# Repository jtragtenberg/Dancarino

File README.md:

# Jerimum
open source IMU

23/10/2015
Fala Rodrigo, novas instruções para o commit "adicionei arquivos de arduino e processing do Motioner para ler RAW e…":

Pelo código estar uma gambiarra só, primeiro estude os quaternions e só depois mande esse código novo pro arduino pra ver os dados RAW... 
e pra te ajudar no descoberta de como os quaternions funcionam:
q = <qw,qx,qy,qz> = <cos(teta/2) , x*sen(teta/2) , y*sen(teta/2) , z*sen(teta/2)>
onde x,y,z é o eixo para onde aponta o vetor que representa o quaternion e teta é o angulo de rotação em torno desse eixo.
tenta descobrir como retornar a partir do quaternion os valores de x,y,z e teta limpos...
Ah! descobri!
olha esse site aqui: http://www.euclideanspace.com/maths/geometry/rotations/conversions/quaternionToAngle/
brincando com uma identidade trigonométrica básia se descobre que:
teta = 2 * acos(qw)
x = qx / sqrt(1-qw*qw)
y = qy / sqrt(1-qw*qw)
z = qz / sqrt(1-qw*qw)

de mão bejada pra tu! (assim fica fácil...)

Depois de ter dominado os quaternions, pra testar o lance com os valores RAW dos sensores, tu faz o seguinte: Pega na pasta /Arduino a pasta IMUDebug. Ali tem o firmware pra mandar os dados calibrados dos sensores e na pasta libraries tem as bibliotecas que ele depende. Tu deve colocar todas as bibliotecas da pasta libraries na pasta do teu computador (X:\My Documents\Arduino\libraries\). Aí tu abre com a ide do arduino o IMUDebug.ino e upa ele pro arduino naquele esquema que eu te falei (escolhe a placa Arduino UNO em Tools>Boards e a porta serial que ele tá em Tools>Serial Port. Aí dá o Run e é só alegria (finger-crossed)
Daí em diante o arduino vai estar com esse firmware e só vai dar pra rodar os novos programas de processing que eu coloquei na pasta /Processing.
São os programas (todos eles levam em conta o magnetometros e as calibrações que já estão na memória EEPROM do arduino): 
IMUVisualization //gera uma visualização a partir dos dados de Yaw Pitch e Roll do sensor e retorna todos os valores de YPR
razorReadYPR //lê direto os valores Yaw Pitch e Roll do sensor
razorReadRaw //lê os valores brutos dos sensores
razorReadGyro //lê só os valores do giroscópio (n tenho certeza se esse funciona)

beleza?

qq coisa a gente se fala

abração.

Oi Rodrigo
O arduino que fiz pra vcs com o MPU6050 e o HMC5883L já está com o código MPU6050_DMP6.
Para fazer o IMU rodar agora, precisa 
- instalar o processing 2;
- clonar esse repositório
- instalar as bibliotecas que estão aqui no git na pasta /Processing/Libraries (pra fazer isso copia as duas pastas pra pasta /Processing/libraries;
- dar três pulinhos
- abrir o código Teapot que ta na pasta Processing
- conectar o arduino no usb
- executar o código do processing
- se aparecer alguma mensagem de erro, da uma olhada no numero das portas seriais e muda a variavel PORT_NUMBER para o numero da porta em que está conectado o arduino. (Se não sabe qual eh a porta tira e ve qual da lista sumiu...). Elas estão expostas na ordem 0, 1, 2,... Vai ser alguma COM# no windows...
- veja o aviãzinho girar com os quaternions...
- descubra agora no código como ele faz isso e se estiver muito pilhado tenta implementar o mesmo código no OpenFrameWorks

abração!

ps. as vezes da um mal contato com o USB e precisa tirar da usb, colocar denovo e reiniciar o código do processing

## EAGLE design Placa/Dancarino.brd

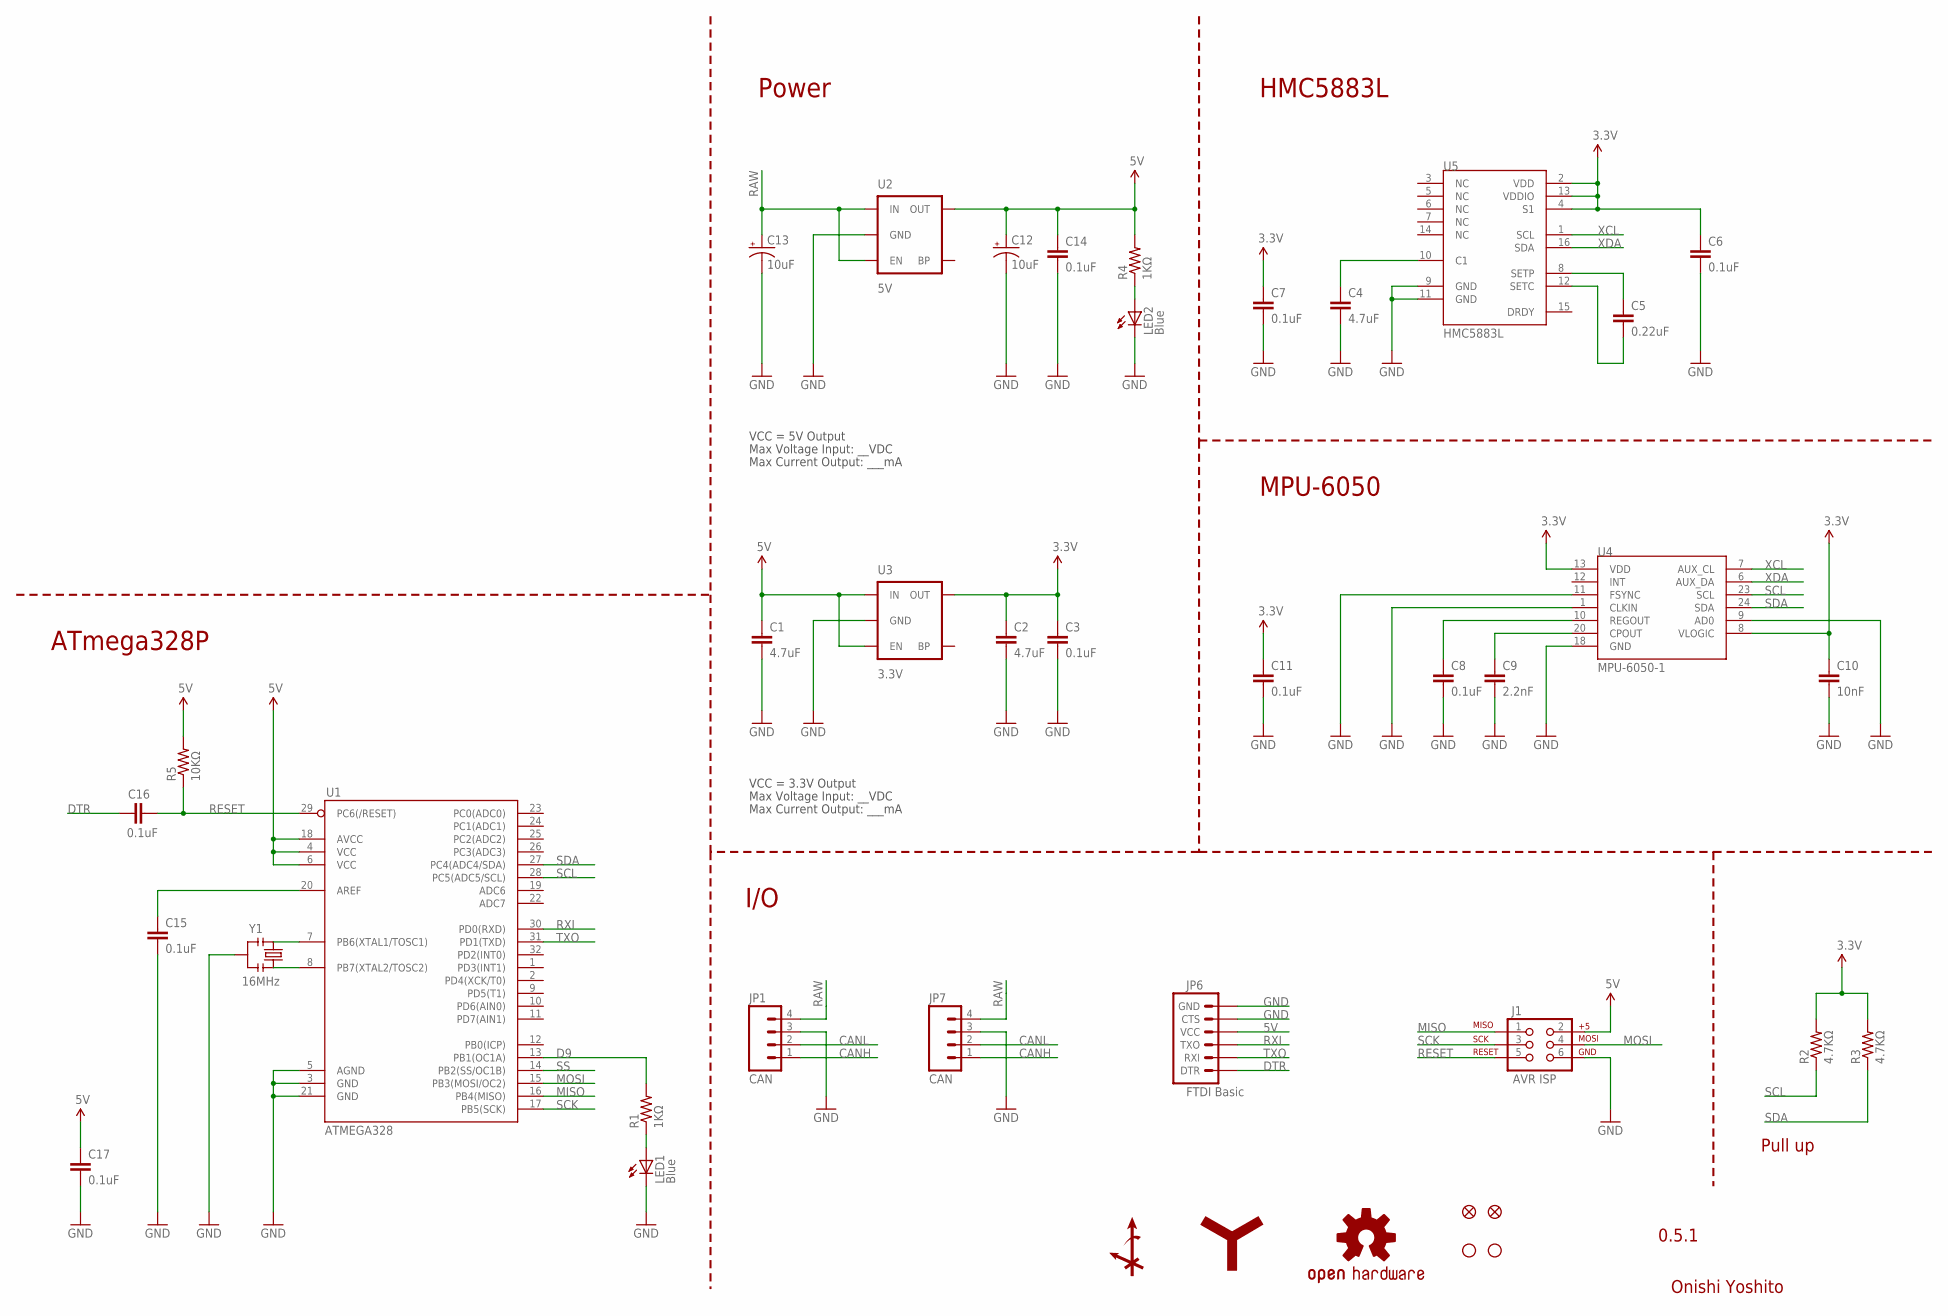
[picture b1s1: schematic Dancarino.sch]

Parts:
C1, C2, C4: 4.7uF; 0402-CAP
C3, C6, C7, C8, C11, C14, C15, C16, C17: 0.1uF; 0402-CAP
C5: 0.22uF; 0402-CAP
C9: 2.2nF; 0402-CAP
C10: 10nF; 0402-CAP
C12, C13: 10uF; EIA3216
J1: AVR ISP; 2X3-NS
JP1, JP7: CAN; JST-4-PTH
JP2, JP5: FIDUCIALUFIDUCIAL; MICRO-FIDUCIAL
JP3, JP4: STAND-OFFTIGHT; STAND-OFF-TIGHT
JP6: FTDI Basic; 1X06
LED1, LED2: Blue; LED-0603
R1, R4: 1KΩ; 0402-RES
R2, R3: 4.7KΩ; 0402-RES
R5: 10KΩ; 0402-RES
U1: ATMEGA328; TQFP32-08
U2: 5V; SOT23-5
U3: 3.3V; SOT23-5
U4: MPU-6050-1; QFN-24-4MM2
U5: HMC5883L; 16LPCC
U$2: OSHW-LOGOS; OSHW-LOGO-S
U$11: AXIS-ANGLE_S
U$13: YCAM_LOGO_L
Y1: 16MHz; RESONATOR-SMD

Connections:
3.3V: C2.1, C3.1, C6.1, C7.1, C10.1, C11.1, R2.2, R3.2, U3.5 (OUT), U4.8 (VLOGIC), U4.13 (VDD), U5.2 (VDD), U5.4 (S1), U5.13 (VDDIO)
5V: C1.1, C12.A (+), C14.1, C17.1, J1.2, JP6.4 (VCC), R4.2, R5.2, U1.4 (VCC), U1.6 (VCC), U1.18 (AVCC), U2.5 (OUT), U3.1 (IN), U3.3 (EN)
CANH: JP1.1, JP7.1
CANL: JP1.2, JP7.2
D9: R1.2, U1.13 (PB1(OC1A))
DTR: C16.1, JP6.1 (DTR)
GND: C1.2, C2.2, C3.2, C4.2, C6.2, C7.2, C8.2, C9.2, C10.2, C11.2, C12.C (-), C13.C (-), C14.2, C15.2, C17.2, J1.6, JP1.3, JP6.5 (CTS), JP6.6 (GND), JP7.3, LED1.C, LED2.C, U1.3 (GND), U1.5 (AGND), U1.21 (GND), U2.2 (GND), U3.2 (GND), U4.1 (CLKIN), U4.9 (AD0), U4.11 (FSYNC), U4.18 (GND), U5.9 (GND), U5.11 (GND), Y1.2
MISO: J1.1, U1.16 (PB4(MISO))
MOSI: J1.4, U1.15 (PB3(MOSI/OC2))
unnamed: LED1.A, R1.1
unnamed: LED2.A, R4.1
unnamed: C4.1, U5.10 (C1)
unnamed: C5.1, U5.8 (SETP)
unnamed: C5.2, U5.12 (SETC)
unnamed: C9.1, U4.20 (CPOUT)
unnamed: C8.1, U4.10 (REGOUT)
unnamed: U1.7 (PB6(XTAL1/TOSC1)), Y1.1
unnamed: U1.8 (PB7(XTAL2/TOSC2)), Y1.3
unnamed: C15.1, U1.20 (AREF)
RAW: C13.A (+), JP1.4, JP7.4, U2.1 (IN), U2.3 (EN)
RESET: C16.2, J1.5, R5.1, U1.29 (PC6(/RESET))
RXI: JP6.3 (TXO), U1.30 (PD0(RXD))
SCK: J1.3, U1.17 (PB5(SCK))
SCL: R2.1, U1.28 (PC5(ADC5/SCL)), U4.23 (SCL)
SDA: R3.1, U1.27 (PC4(ADC4/SDA)), U4.24 (SDA)
SS: U1.14 (PB2(SS/OC1B))
TXO: JP6.2 (RXI), U1.31 (PD1(TXD))
XCL: U4.7 (AUX_CL), U5.1 (SCL)
XDA: U4.6 (AUX_DA), U5.16 (SDA)

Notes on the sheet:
Onishi Yoshito
0.5.1
HMC5883L
MPU-6050
Pull up
Max Voltage Input: __VDC
Max Current Output: ___mA
VCC = 3.3V Output
VCC = 5V Output
ATmega328P
Power
I/O

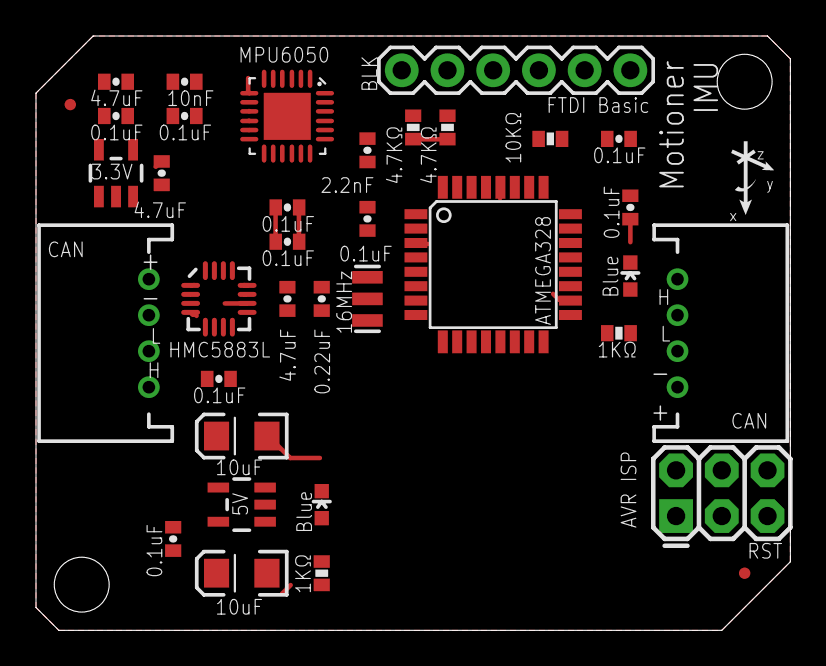
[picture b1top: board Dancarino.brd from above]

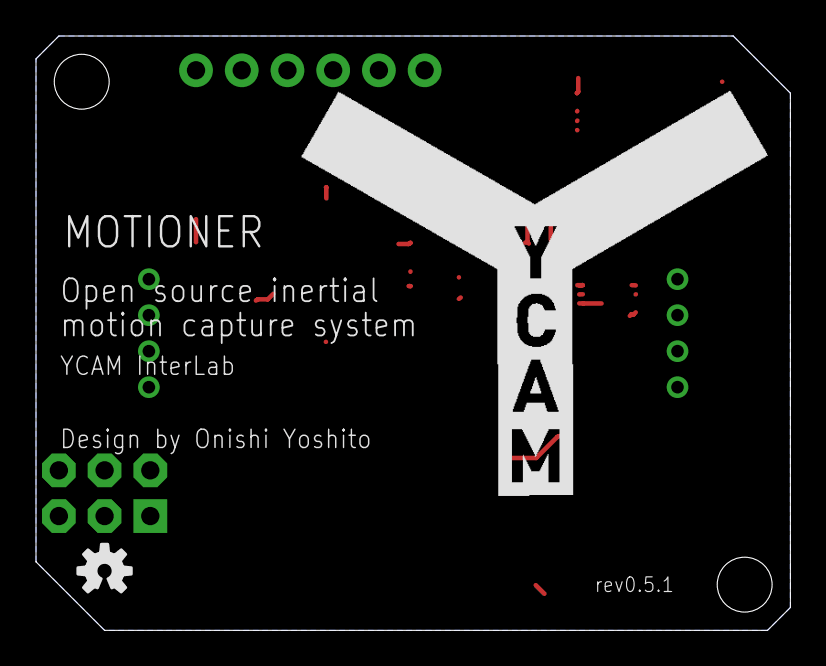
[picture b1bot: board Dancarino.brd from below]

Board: 2 copper layers, 41.9 x 33.0 mm, 41 parts (2 on the bottom side), 28 nets.

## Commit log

2015-10-09 primeiro commit
2015-10-09 deixei a porta serial mais facil de mudar no teapot
2015-10-09 Create README.md
    primeira descrição pro Rodrigo
2015-10-09 ps: bug
2015-10-23 adicionei arquivos de arduino e processing do Motioner para ler RAW e YPR values
2015-11-10 libraries dos dois firmwares
2015-11-10 libraries
2015-11-10 teste
2015-11-10 testes novos
2015-11-17 kickGyro
2015-11-17 arquivos reorganizados
2015-11-19 Jerimum no ar!
2015-12-04 A volta de Franklin
2015-12-08 GUI Melhorada
2015-12-08 posição inicial do getSeed, Seeds com MIDI_Channel e coloquei classe de EffectsPadXY
2015-12-08 GiroMouse
2015-12-08 ajustezinho na GUI
2015-12-09 Gráfico, melhoria no OnsetModule (sem noteOff)
2015-12-09 NoteOff temporário
2015-12-09 Save Load Import Export
2015-12-09 Botoes na interface, nome de arquivos de config e atalhos atualizados
2015-12-09 feedBack visual do trigger MIDI
2015-12-10 voltou a funcionar!
2015-12-10 giroMouse integrado com Jerimum
2015-12-10 giro mouse incorporado na clase Effects

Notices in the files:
parts and their libraries:
SparkFun-Sensors: Licensing: CC v3.0 Share-Alike You are welcome to use this library for commercial purposes.
